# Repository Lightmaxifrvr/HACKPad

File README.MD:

# SIWWYPAD!
This is my [HackClub](https://hackclub.com/) [HackPad](https://hackpad.hackclub.com/) Project!
It has 9 Keys, 4 LED's, a Rotary Encoder and uses KMK firmware.

## hacpad!
This is it this is the hackpad in all its glory (minus the keycaps).

## the schem!
Its pretty simple and probably the best looking thing out of everything.

## the Pee Cee Bee!
The PCB in the KiCad View.

## the Case.
This is the case together (using m3 bolts)

## the Bill (Cypher) of Materials!

1x Seeed XIAO RP2040
9x Through-hole 1N4148 Diodes
9x Cherry MX Switches
1x EC11 Rotary encoder
9x Red DSA keycaps
4x SK6812 MINI-E LEDs
4x M3x16mm screws
4x M3x5mx4mm heatset inserts

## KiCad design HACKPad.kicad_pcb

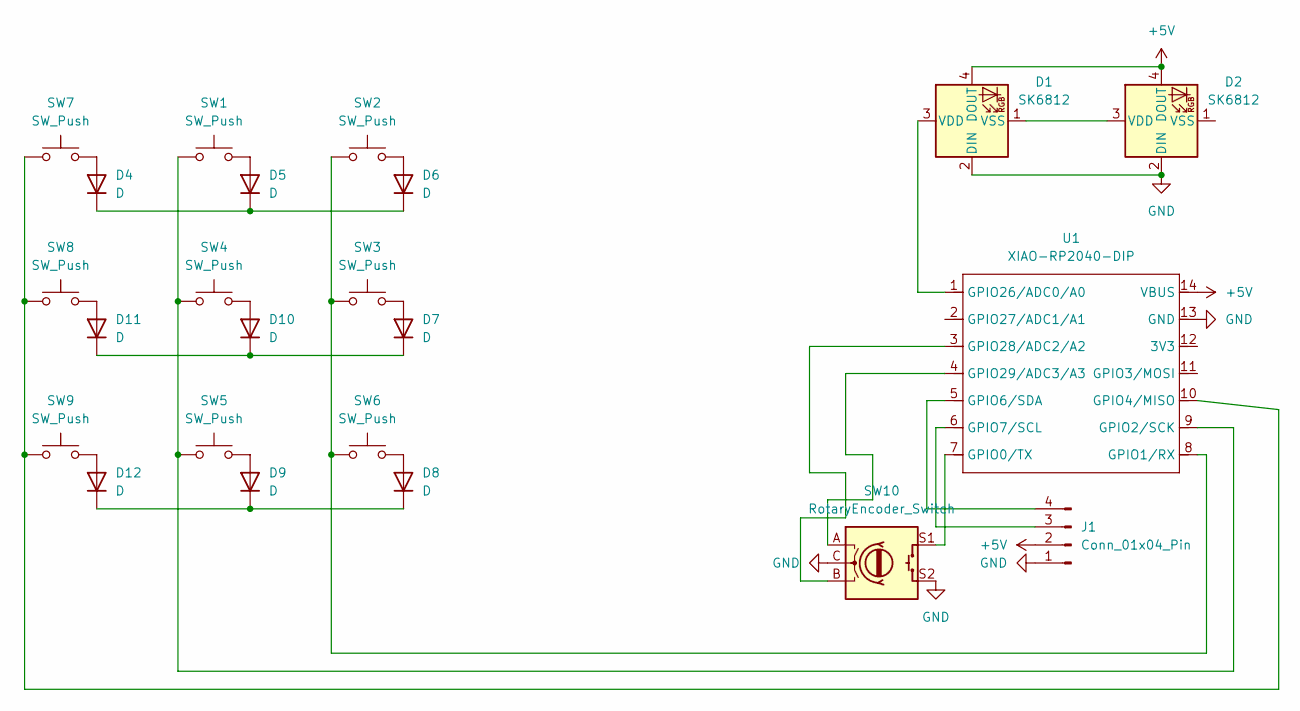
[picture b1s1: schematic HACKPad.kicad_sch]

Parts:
D1, D2: SK6812; LED_SK6812_PLCC4_5.0x5.0mm_P3.2mm
D4, D5, D6, D7, D8, D9, D10, D11, D12: D; D_DO-35_SOD27_P7.62mm_Horizontal
J1: Conn_01x04_Pin; MODULE_DM-OLED096-636
SW1, SW2, SW3, SW4, SW5, SW6, SW7, SW8, SW9: SW_Push; SW_Cherry_MX_1.00u_PCB
SW10: RotaryEncoder_Switch; RotaryEncoder_Alps_EC11E-Switch_Vertical_H20mm_CircularMoun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
U1: XIAO-RP2040-DIP

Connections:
+5V: D1.4 (DOUT), D2.4 (DOUT), J1.2, U1.14 (VBUS)
GND: D1.2 (DIN), D2.2 (DIN), J1.1, SW10.C, SW10.S2, U1.13 (GND)
unnamed: D1.3 (VDD), U1.1 (GPIO26/ADC0/A0)
unnamed: D1.1 (VSS), D2.3 (VDD)
unnamed: D4.2 (A), SW7.2
unnamed: D4.1 (K), D5.1 (K), D6.1 (K)
unnamed: D5.2 (A), SW1.2
unnamed: D6.2 (A), SW2.2
unnamed: D7.2 (A), SW3.2
unnamed: D8.2 (A), SW6.2
unnamed: D9.2 (A), SW5.2
unnamed: D10.2 (A), SW4.2
unnamed: D7.1 (K), D10.1 (K), D11.1 (K)
unnamed: D11.2 (A), SW8.2
unnamed: D12.2 (A), SW9.2
unnamed: D8.1 (K), D9.1 (K), D12.1 (K)
unnamed: J1.3, U1.6 (GPIO7/SCL)
unnamed: J1.4, U1.5 (GPIO6/SDA)
unnamed: SW10.S1, U1.7 (GPIO0/TX)
unnamed: SW2.1, SW3.1, SW6.1, U1.8 (GPIO1/RX)
unnamed: SW1.1, SW4.1, SW5.1, U1.9 (GPIO2/SCK)
unnamed: SW7.1, SW8.1, SW9.1, U1.10 (GPIO4/MISO)
unnamed: SW10.B, U1.3 (GPIO28/ADC2/A2)
unnamed: SW10.A, U1.4 (GPIO29/ADC3/A3)

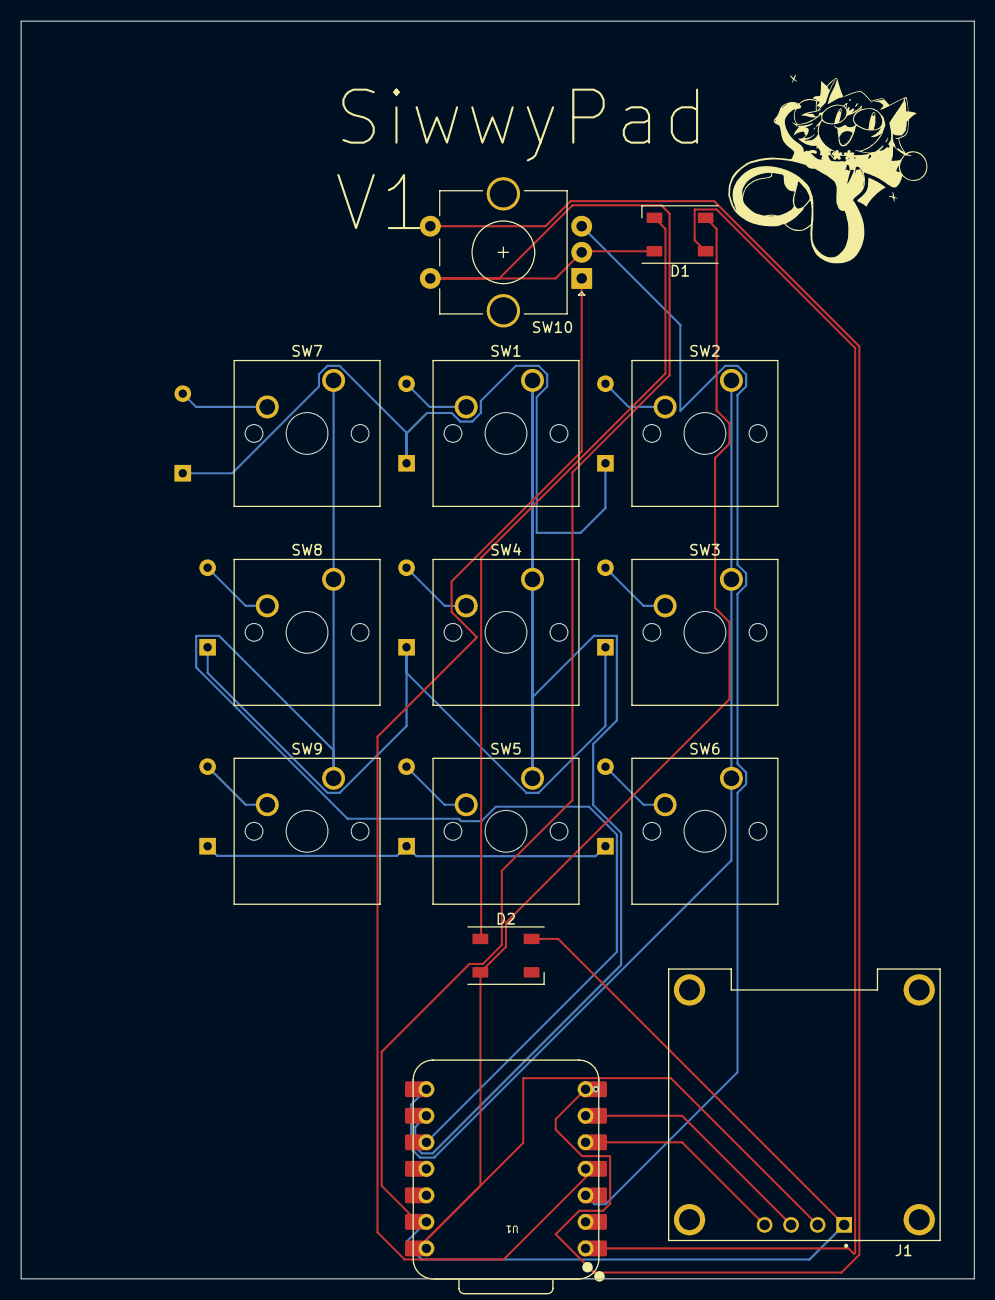
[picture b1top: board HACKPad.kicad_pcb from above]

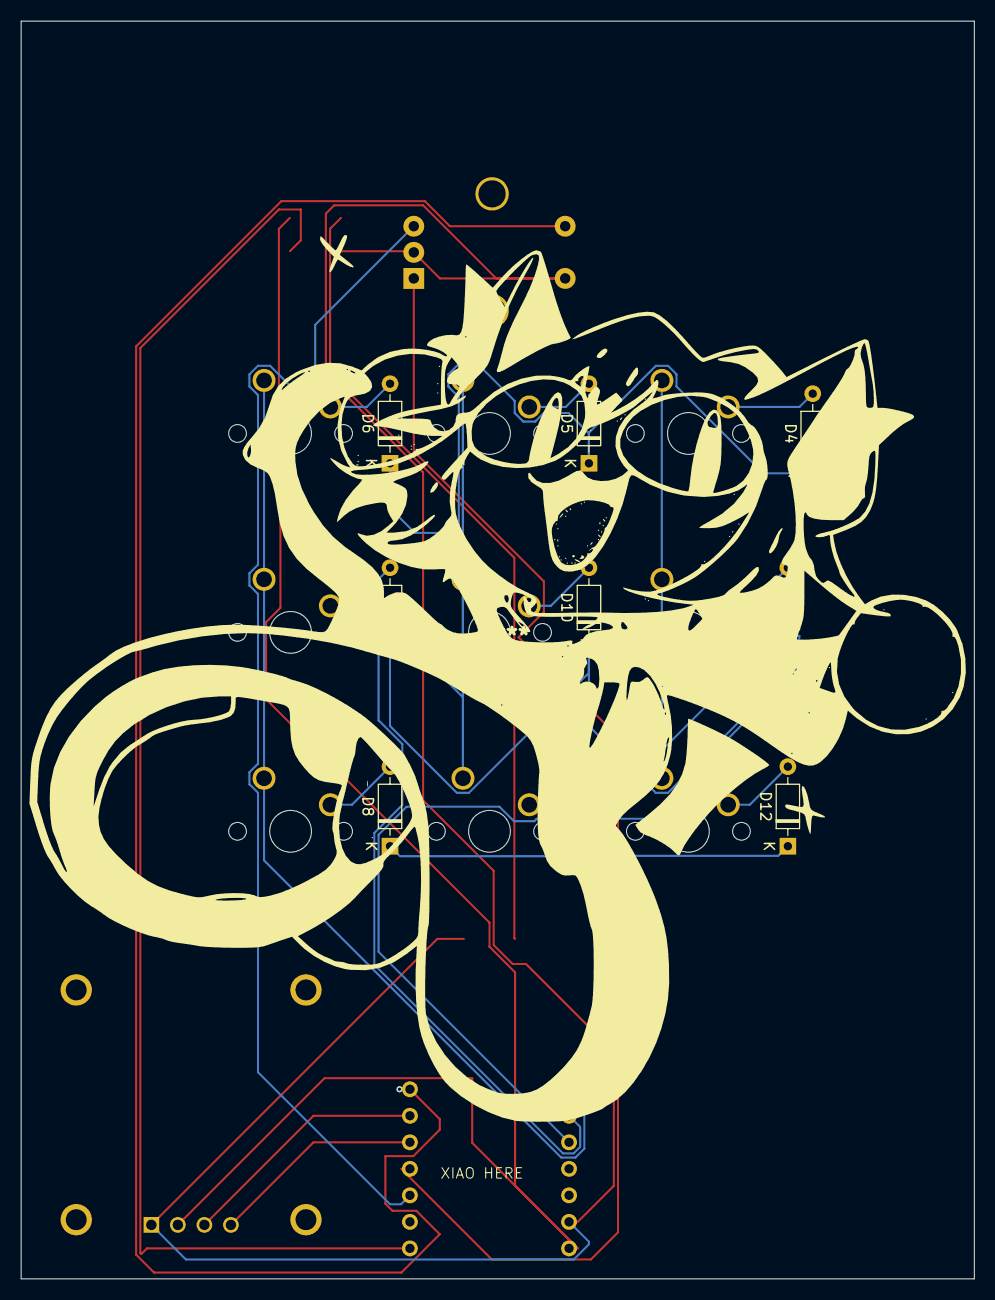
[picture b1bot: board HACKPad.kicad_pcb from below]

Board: 2 copper layers, 91.3 x 120.4 mm, 23 parts (9 on the bottom side), 24 nets.

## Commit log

2025-02-19 removed backups
2025-02-19 added README.MD and generally everything
